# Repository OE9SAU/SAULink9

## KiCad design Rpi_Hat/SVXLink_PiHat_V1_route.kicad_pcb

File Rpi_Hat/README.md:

# SAULink9 RPiHat

PiHat for Rpi3B+, give space to some GPIOs and connection point to the SAULink9 front panel

## Highlights
  * front panel connection point
  * Convenient access to 4 GPIOs (for relays or other circuits)
  * FET-controlled fan output
  * Dedicated 1-Wire port
  * External voltage detection via optocoupler
  * Extra DIY prototyping space

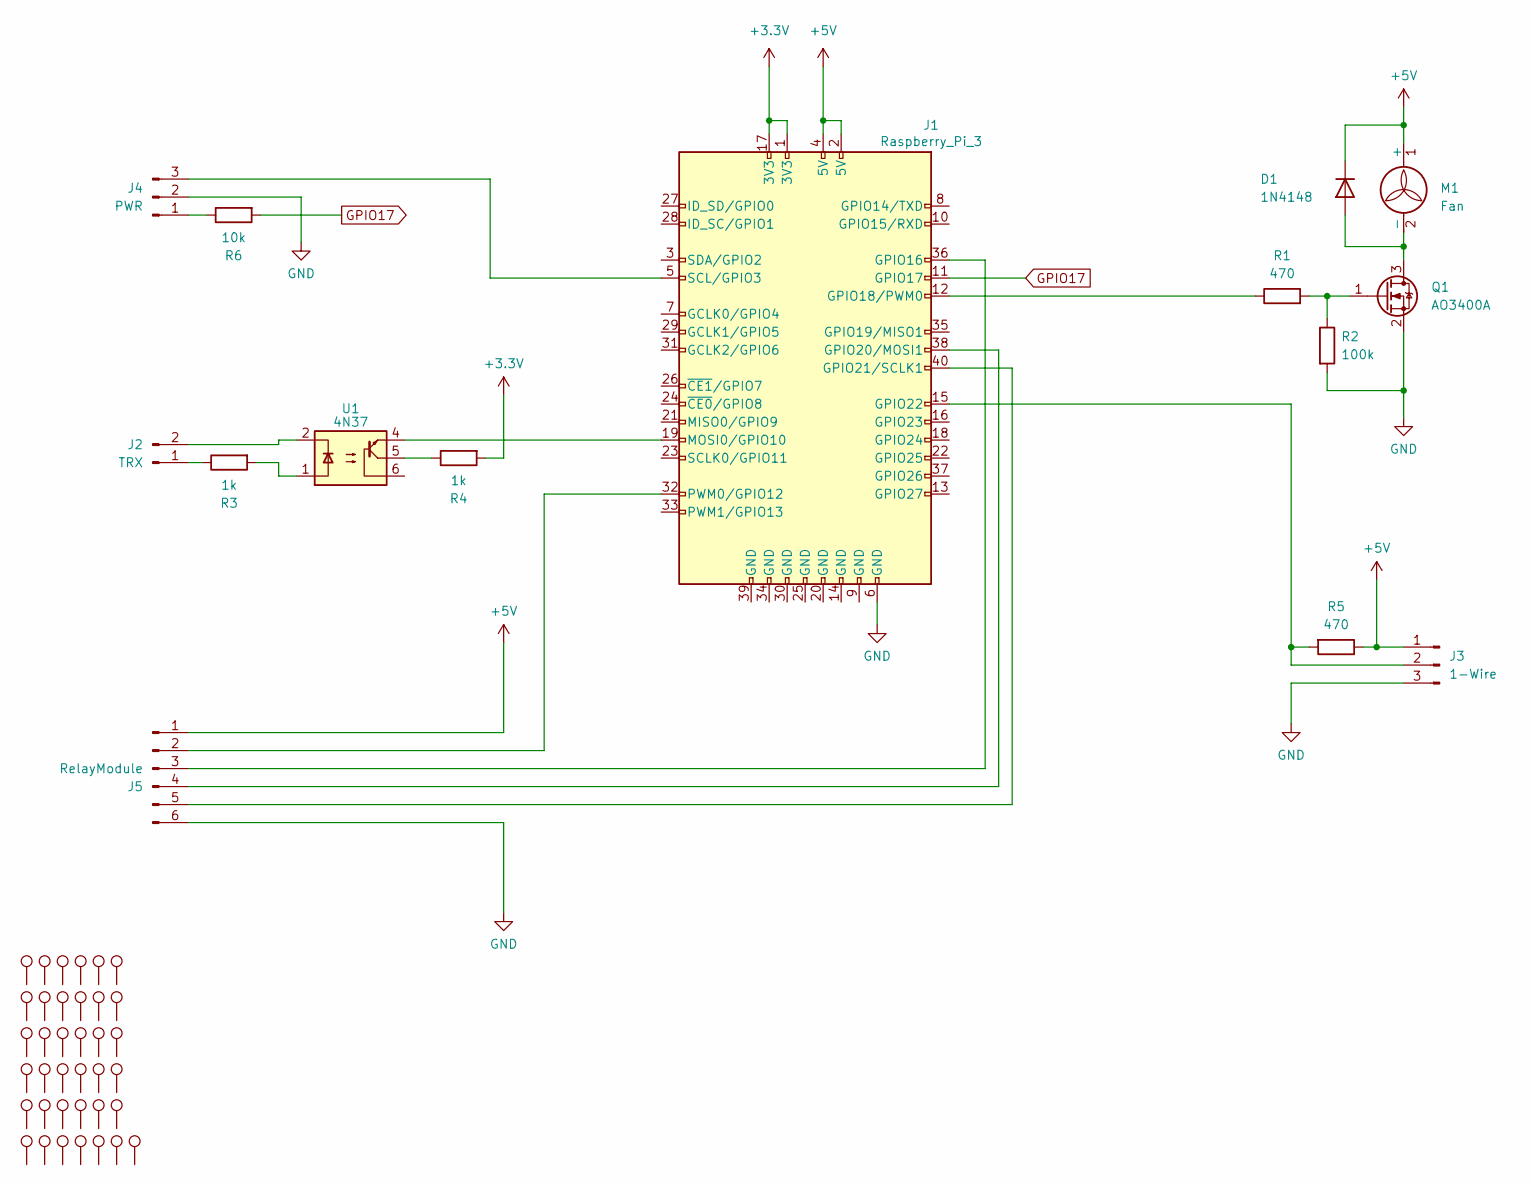
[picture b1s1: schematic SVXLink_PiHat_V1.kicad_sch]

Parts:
D1: 1N4148; D_SOD-123
J1: Raspberry_Pi_3; ESQ-120-14-T-D
J2: TRX; PinHeader_1x02_P2.54mm_Horizontal
J3: 1-Wire; PinHeader_1x03_P2.54mm_Horizontal
J4: PWR; PinHeader_1x03_P2.54mm_Horizontal
J5: RelayModule; PinHeader_1x06_P2.54mm_Horizontal
M1: Fan; PinHeader_1x02_P2.54mm_Horizontal
Q1: AO3400A; SOT-23
R1, R5: 470; R_0805_2012Metric_Pad1.20x1.40mm_HandSolder
R2: 100k; R_0805_2012Metric_Pad1.20x1.40mm_HandSolder
R3, R4: 1k; R_0805_2012Metric_Pad1.20x1.40mm_HandSolder
R6: 10k; R_0805_2012Metric_Pad1.20x1.40mm_HandSolder
TP1, TP2, TP3, TP4, TP5, TP6, TP7, TP8, TP9, TP10, TP11, TP12, TP13, TP14, TP15, TP16, TP17, TP18, TP19, TP20, TP21, TP22, TP23, TP24, TP25, TP26, TP27, TP28, TP29, TP30, TP31, TP32, TP33, TP34, TP35, TP36, TP37: TestPoint; TestPoint_THTPad_D2.0mm_Drill1.0mm
U1: 4N37; DIP-6_W7.62mm

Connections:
+3.3V: J1.1 (3V3), J1.17 (3V3), R4.2
+5V: D1.1 (K), J1.2 (5V), J1.4 (5V), J3.1, J5.1, M1.1 (+), R5.1, TP1.1, TP6.1, TP11.1, TP16.1, TP21.1, TP26.1, TP31.1
GND: J1.6 (GND), J3.3, J4.2, J5.6, Q1.2 (S), R2.2, TP2.1, TP7.1, TP12.1, TP17.1, TP22.1, TP27.1; also elsewhere on the board
GPIO17: J1.11 (GPIO17), R6.2
unnamed: D1.2 (A), M1.2 (-), Q1.3 (D)
unnamed: J1.36 (GPIO16), J5.3
unnamed: J1.12 (GPIO18/PWM0), R1.1
unnamed: J1.38 (GPIO20/MOSI1), J5.4
unnamed: J1.40 (GPIO21/SCLK1), J5.5
unnamed: J1.15 (GPIO22), J3.2, R5.2
unnamed: J1.19 (MOSI0/GPIO10), U1.4
unnamed: J1.32 (PWM0/GPIO12), J5.2
unnamed: J1.5 (SCL/GPIO3), J4.3
unnamed: J2.1, R3.1
unnamed: J2.2, U1.2
unnamed: J4.1, R6.1
unnamed: Q1.1 (G), R1.2, R2.1
unnamed: R3.2, U1.1
unnamed: R4.1, U1.5

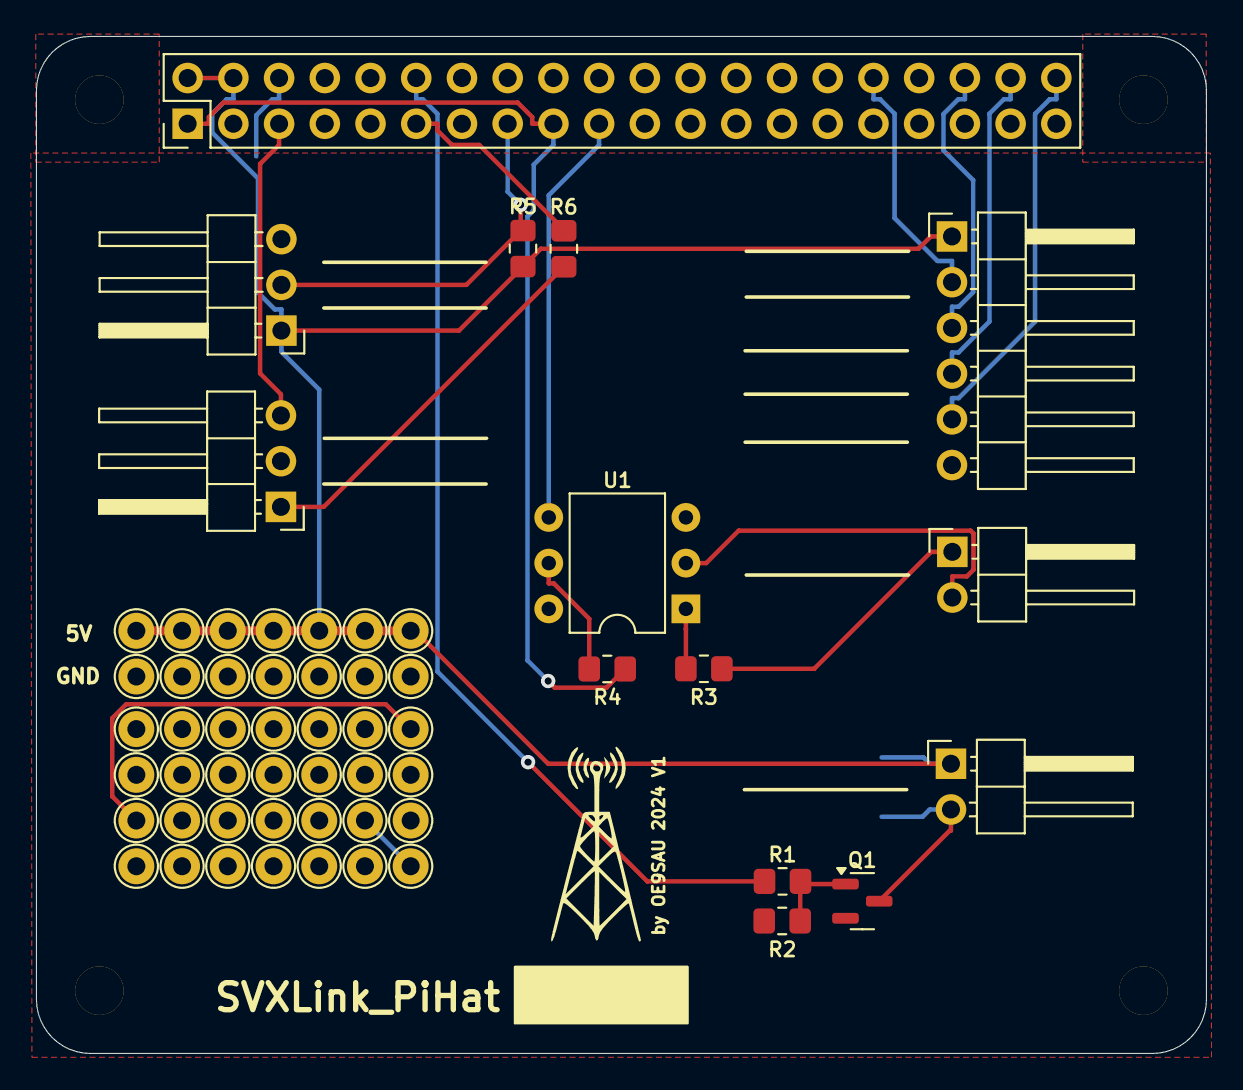
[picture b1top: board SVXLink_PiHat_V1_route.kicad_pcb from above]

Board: 2 copper layers, 65.0 x 56.5 mm, 62 parts (1 on the bottom side), 19 nets.

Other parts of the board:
G1: LOGO
REF1, REF2, REF3, REF4: MountingHole_2.7mm_M2.5
TP311, TP321, TP333, TP341, TP351: TestPoint; TestPoint_THTPad_D2.0mm_Drill1.0mm

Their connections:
GND: TP321.1; also elsewhere on the board

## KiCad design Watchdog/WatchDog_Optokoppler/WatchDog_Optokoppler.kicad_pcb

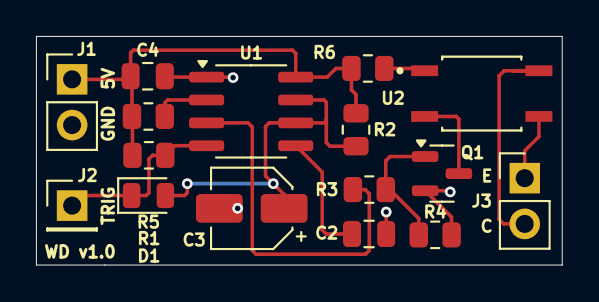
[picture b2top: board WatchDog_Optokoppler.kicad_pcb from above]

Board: 2 copper layers, 29.2 x 12.7 mm, 16 parts (0 on the bottom side), 12 nets.

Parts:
C2: 10nF; C_0805_2012Metric
C3: 100uF/16V; CP_Elec_4x5.7
C4: 100nF; C_0805_2012Metric
D1: 1N4148; D_0805_2012Metric
J1: +5V; PinHeader_1x02_P2.54mm_Vertical
J2: Trigger; PinHeader_1x01_P2.54mm_Vertical
J3: REMOTE-CONTACT; PinHeader_1x02_P2.54mm_Vertical
Q1: AO3400A; SOT-23
R1, R5: 10k; R_0805_2012Metric
R2: 270K; R_0805_2012Metric
R3: 100R; R_0805_2012Metric
R4: 100k; R_0805_2012Metric
R6: 680R; R_0805_2012Metric
U1: NE555D; SOIC-8_3.9x4.9mm_P1.27mm
U2: EL357N-G; OPTO_EL357N-G

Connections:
GND: C2.1, C3.2, C4.1, J1.2, Q1.2 (S), R4.1, U1.1 (GND)
unnamed: C3.1, D1.2 (A), R2.2, U1.6 (THR), U1.7 (DIS)
unnamed: D1.1 (K), J2.1, R1.2, U1.4 (R)
unnamed: C4.2, J1.1, R1.1, R2.1, R5.2, R6.2, U1.8 (VCC)
unnamed: J3.1, U2.3
unnamed: J3.2, U2.4
unnamed: Q1.3 (D), U2.2
unnamed: Q1.1 (G), R3.2, R4.2
unnamed: R6.1, U2.1
unnamed: C2.2, U1.5 (CV)
unnamed: R3.1, U1.3 (Q)
unnamed: R5.1, U1.2 (TR)
